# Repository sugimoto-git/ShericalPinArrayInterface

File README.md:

# ShericalPinArrayInterface
球体ピンアレイインターフェースのファームウェア、筐体の3Dデータ、論文を管理する

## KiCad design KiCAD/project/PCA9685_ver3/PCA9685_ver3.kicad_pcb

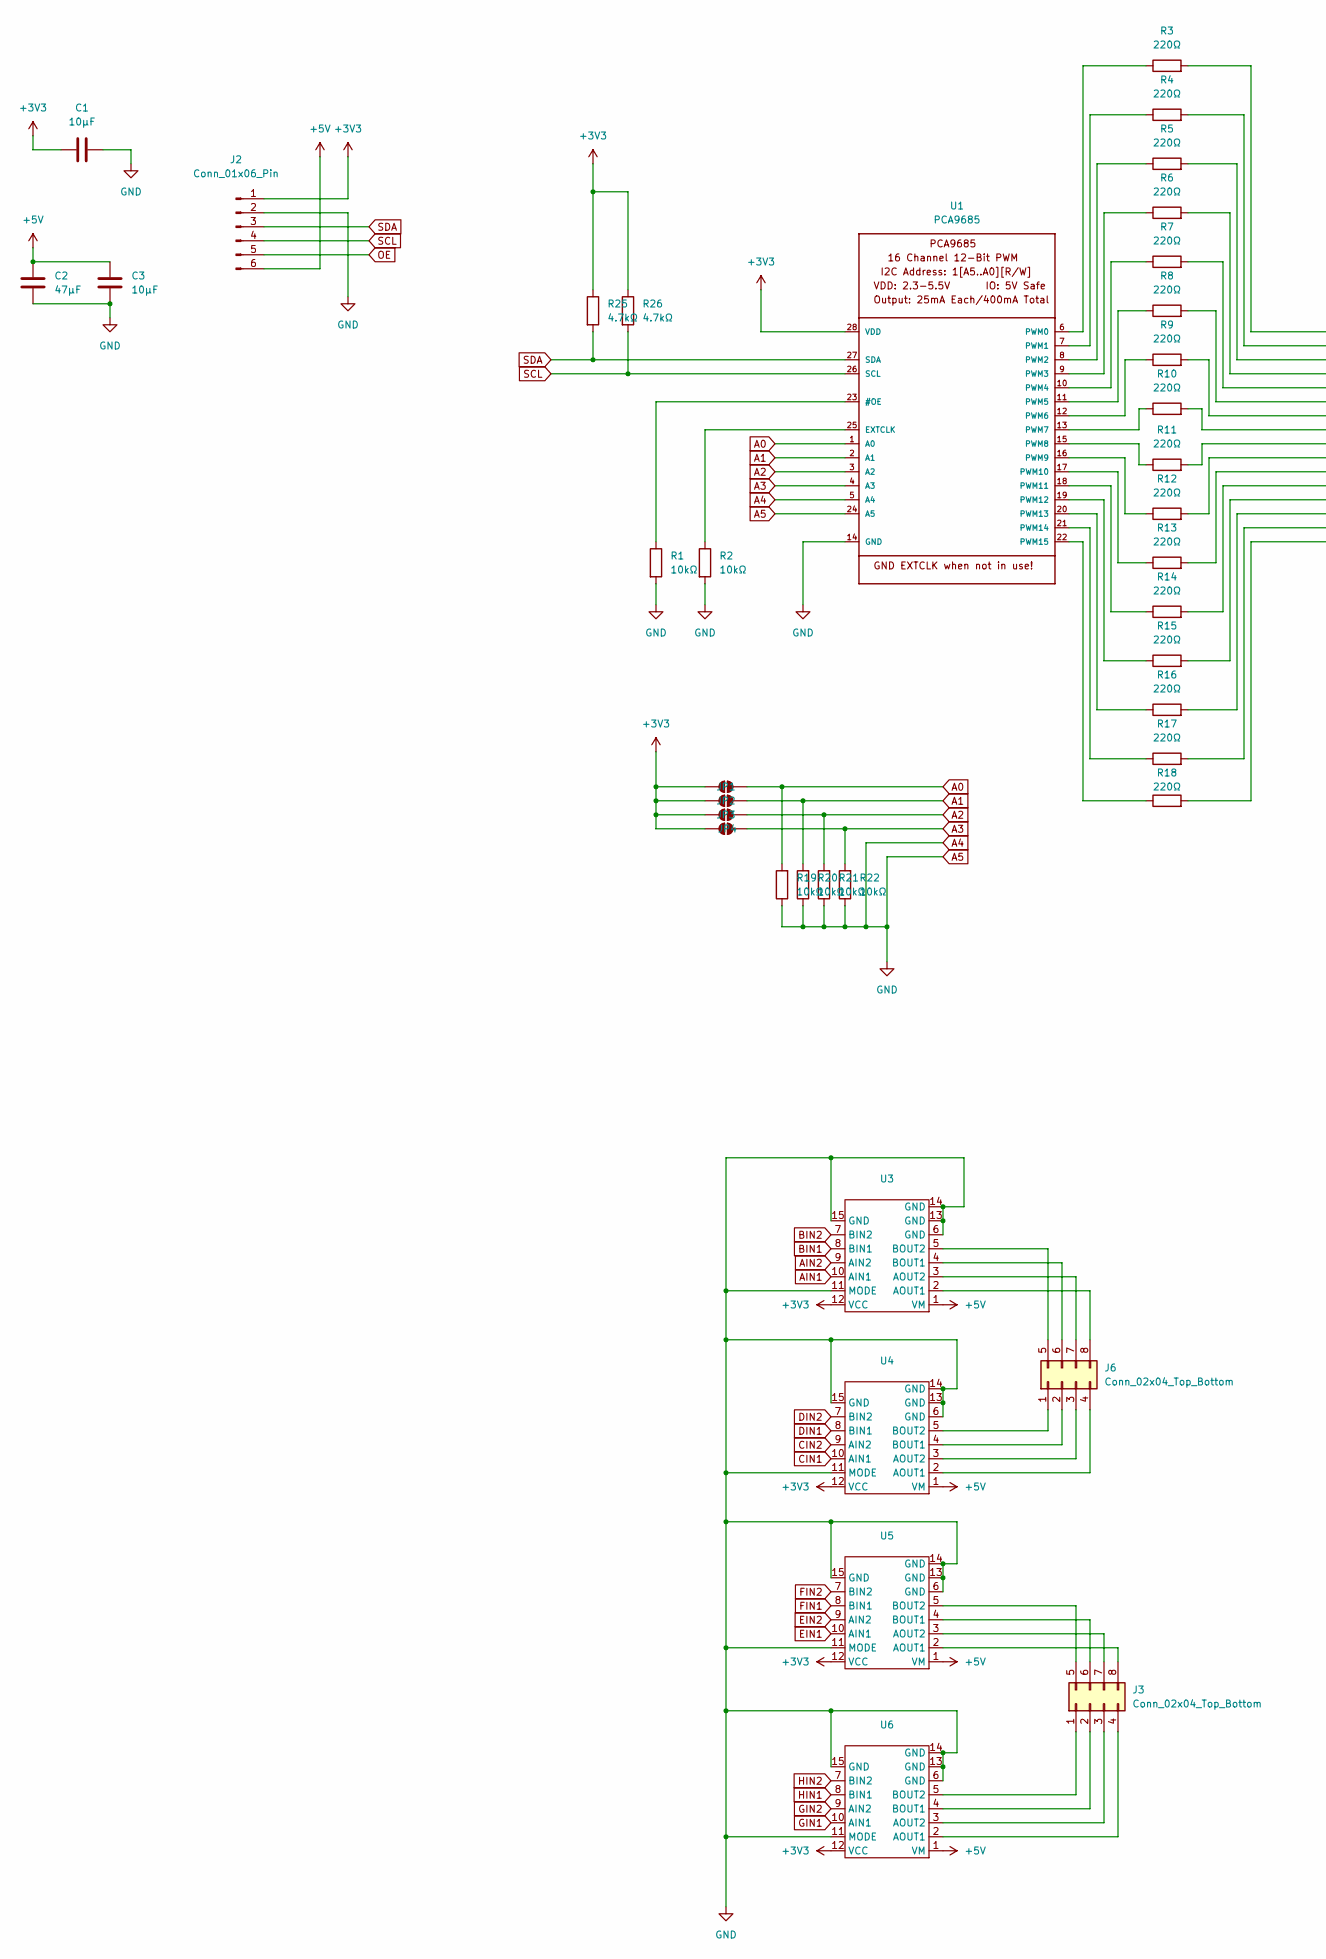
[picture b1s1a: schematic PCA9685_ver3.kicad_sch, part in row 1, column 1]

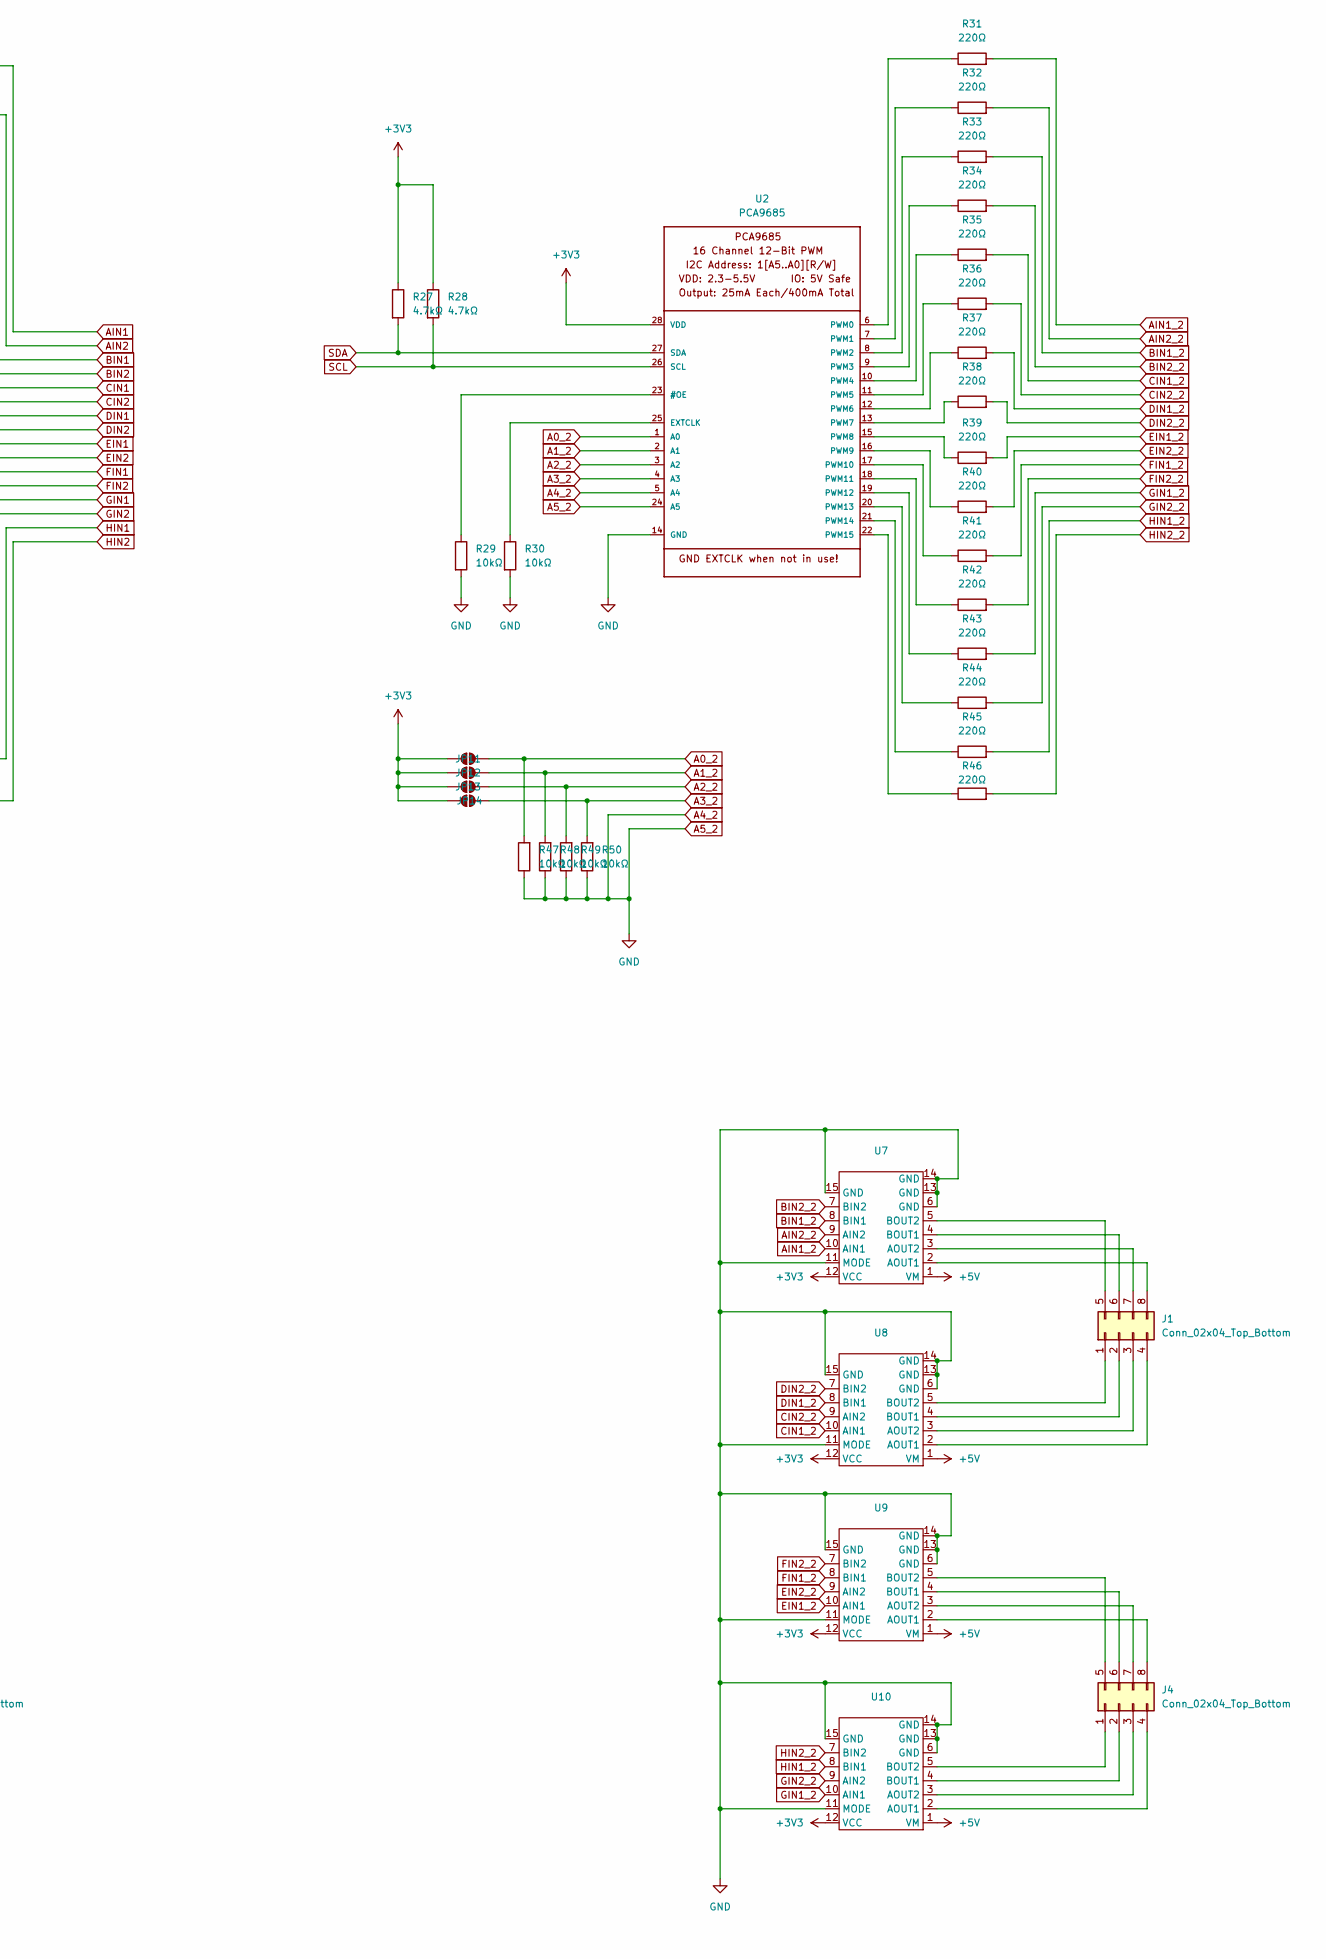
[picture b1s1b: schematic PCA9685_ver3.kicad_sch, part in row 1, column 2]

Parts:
C1, C3: 10μF; C_0603_1608Metric
C2: 47μF; C_0805_2012Metric
J1, J3, J4, J6: Conn_02x04_Top_Bottom; PinHeader_2x04_P2.54mm_Horizontal
J2: Conn_01x06_Pin; PinHeader_1x06_P2.54mm_Horizontal
JP1, JP2, JP3, JP4, JP11, JP12, JP13, JP14: SolderJumper_2_Open; SolderJumper-2_P1.3mm_Open_RoundedPad1.0x1.5mm
R1, R2, R19, R20, R21, R22, R29, R30, R47, R48, R49, R50: 10kΩ; R_0402_1005Metric
R3, R4, R5, R6, R7, R8, R9, R10, R11, R12, R13, R14, R15, R16, R17, R18, R31, R32, R33, R34, R35, R36, R37, R38, R39, R40, R41, R42, R43, R44, R45, R46: 220Ω; R_0402_1005Metric
R25, R26, R27, R28: 4.7kΩ; R_0805_2012Metric
U1, U2: PCA9685; TSSOP-28_4.4x9.7mm_P0.65mm
U3, U4, U5, U6, U7, U8, U9, U10: SON50P300X200X80-13N

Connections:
+3V3: C1.1, J2.1, JP1.1 (A), JP2.1 (A), JP3.1 (A), JP4.1 (A), JP11.1 (A), JP12.1 (A), JP13.1 (A), JP14.1 (A), R25.1, R26.1, R27.1, R28.1, U1.28 (VDD), U2.28 (VDD), U3.12 (VCC), U4.12 (VCC), U5.12 (VCC), U6.12 (VCC), U7.12 (VCC), U8.12 (VCC), U9.12 (VCC), U10.12 (VCC)
+5V: C2.1, C3.1, J2.6, U3.1 (VM), U4.1 (VM), U5.1 (VM), U6.1 (VM), U7.1 (VM), U8.1 (VM), U9.1 (VM), U10.1 (VM)
A0: JP1.2 (B), R19.2, U1.1 (A0)
A0_2: JP11.2 (B), R47.2, U2.1 (A0)
A1: JP2.2 (B), R20.2, U1.2 (A1)
A1_2: JP12.2 (B), R48.2, U2.2 (A1)
A2: JP3.2 (B), R21.2, U1.3 (A2)
A2_2: JP13.2 (B), R49.2, U2.3 (A2)
A3: JP4.2 (B), R22.2, U1.4 (A3)
A3_2: JP14.2 (B), R50.2, U2.4 (A3)
A4: C1.2, C2.2, C3.2, J2.2, R1.2, R2.2, R19.1, R20.1, R21.1, R22.1, R29.2, R30.2, R47.1, R48.1, R49.1, R50.1, U1.5 (A4), U1.14 (GND), U1.24 (A5), U2.5 (A4), U2.14 (GND), U2.24 (A5), U3.6 (GND), U3.11 (MODE), U3.13 (GND), U3.14 (GND), U3.15 (GND), U4.6 (GND), U4.11 (MODE), U4.13 (GND), U4.14 (GND), U4.15 (GND), U5.6 (GND), U5.11 (MODE), U5.13 (GND), U5.14 (GND), U5.15 (GND), U6.6 (GND), U6.11 (MODE), U6.13 (GND), U6.14 (GND), U6.15 (GND), U7.6 (GND), U7.11 (MODE), U7.13 (GND), U7.14 (GND), U7.15 (GND), U8.6 (GND), U8.11 (MODE), U8.13 (GND), U8.14 (GND), U8.15 (GND), U9.6 (GND), U9.11 (MODE), U9.13 (GND), U9.14 (GND), U9.15 (GND), U10.6 (GND), U10.11 (MODE), U10.13 (GND), U10.14 (GND), U10.15 (GND)
AIN1: R3.2, U3.10 (AIN1)
AIN1_2: R31.2, U7.10 (AIN1)
AIN2: R4.2, U3.9 (AIN2)
AIN2_2: R32.2, U7.9 (AIN2)
BIN1: R5.2, U3.8 (BIN1)
BIN1_2: R33.2, U7.8 (BIN1)
BIN2: R6.2, U3.7 (BIN2)
BIN2_2: R34.2, U7.7 (BIN2)
CIN1: R7.2, U4.10 (AIN1)
CIN1_2: R35.2, U8.10 (AIN1)
CIN2: R8.2, U4.9 (AIN2)
CIN2_2: R36.2, U8.9 (AIN2)
DIN1: R9.2, U4.8 (BIN1)
DIN1_2: R37.2, U8.8 (BIN1)
DIN2: R10.2, U4.7 (BIN2)
DIN2_2: R38.2, U8.7 (BIN2)
EIN1: R11.2, U5.10 (AIN1)
EIN1_2: R39.2, U9.10 (AIN1)
EIN2: R12.2, U5.9 (AIN2)
EIN2_2: R40.2, U9.9 (AIN2)
FIN1: R13.2, U5.8 (BIN1)
FIN1_2: R41.2, U9.8 (BIN1)
FIN2: R14.2, U5.7 (BIN2)
FIN2_2: R42.2, U9.7 (BIN2)
GIN1: R15.2, U6.10 (AIN1)
GIN1_2: R43.2, U10.10 (AIN1)
GIN2: R16.2, U6.9 (AIN2)
GIN2_2: R44.2, U10.9 (AIN2)
HIN1: R17.2, U6.8 (BIN1)
HIN1_2: R45.2, U10.8 (BIN1)
HIN2: R18.2, U6.7 (BIN2)
HIN2_2: R46.2, U10.7 (BIN2)
unnamed: J1.1, U8.5 (BOUT2)
unnamed: J1.2, U8.4 (BOUT1)
unnamed: J1.3, U8.3 (AOUT2)
unnamed: J1.4, U8.2 (AOUT1)
unnamed: J1.5, U7.5 (BOUT2)
unnamed: J1.6, U7.4 (BOUT1)
unnamed: J1.7, U7.3 (AOUT2)
unnamed: J1.8, U7.2 (AOUT1)
unnamed: J3.1, U6.5 (BOUT2)
unnamed: J3.2, U6.4 (BOUT1)
unnamed: J3.3, U6.3 (AOUT2)
unnamed: J3.4, U6.2 (AOUT1)
unnamed: J3.5, U5.5 (BOUT2)
unnamed: J3.6, U5.4 (BOUT1)
unnamed: J3.7, U5.3 (AOUT2)
unnamed: J3.8, U5.2 (AOUT1)
unnamed: J4.1, U10.5 (BOUT2)
unnamed: J4.2, U10.4 (BOUT1)
unnamed: J4.3, U10.3 (AOUT2)
unnamed: J4.4, U10.2 (AOUT1)
unnamed: J4.5, U9.5 (BOUT2)
unnamed: J4.6, U9.4 (BOUT1)
unnamed: J4.7, U9.3 (AOUT2)
unnamed: J4.8, U9.2 (AOUT1)
unnamed: J6.1, U4.5 (BOUT2)
unnamed: J6.2, U4.4 (BOUT1)
unnamed: J6.3, U4.3 (AOUT2)
unnamed: J6.4, U4.2 (AOUT1)
unnamed: J6.5, U3.5 (BOUT2)
unnamed: J6.6, U3.4 (BOUT1)
unnamed: J6.7, U3.3 (AOUT2)
unnamed: J6.8, U3.2 (AOUT1)
unnamed: R1.1, U1.23 (#OE)
unnamed: R2.1, U1.25 (EXTCLK)
unnamed: R3.1, U1.6 (PWM0)
unnamed: R4.1, U1.7 (PWM1)
unnamed: R5.1, U1.8 (PWM2)
unnamed: R6.1, U1.9 (PWM3)
unnamed: R7.1, U1.10 (PWM4)
unnamed: R8.1, U1.11 (PWM5)
unnamed: R9.1, U1.12 (PWM6)
unnamed: R10.1, U1.13 (PWM7)
unnamed: R11.1, U1.15 (PWM8)
unnamed: R12.1, U1.16 (PWM9)
unnamed: R13.1, U1.17 (PWM10)
unnamed: R14.1, U1.18 (PWM11)
unnamed: R15.1, U1.19 (PWM12)
unnamed: R16.1, U1.20 (PWM13)
unnamed: R17.1, U1.21 (PWM14)
unnamed: R18.1, U1.22 (PWM15)
unnamed: R29.1, U2.23 (#OE)
unnamed: R30.1, U2.25 (EXTCLK)
unnamed: R31.1, U2.6 (PWM0)
unnamed: R32.1, U2.7 (PWM1)
unnamed: R33.1, U2.8 (PWM2)
unnamed: R34.1, U2.9 (PWM3)
unnamed: R35.1, U2.10 (PWM4)
unnamed: R36.1, U2.11 (PWM5)
unnamed: R37.1, U2.12 (PWM6)
unnamed: R38.1, U2.13 (PWM7)
unnamed: R39.1, U2.15 (PWM8)
unnamed: R40.1, U2.16 (PWM9)
unnamed: R41.1, U2.17 (PWM10)
unnamed: R42.1, U2.18 (PWM11)
unnamed: R43.1, U2.19 (PWM12)
unnamed: R44.1, U2.20 (PWM13)
unnamed: R45.1, U2.21 (PWM14)
unnamed: R46.1, U2.22 (PWM15)
OE: J2.5
SCL: J2.4, R26.2, R28.2, U1.26 (SCL), U2.26 (SCL)
SDA: J2.3, R25.2, R27.2, U1.27 (SDA), U2.27 (SDA)

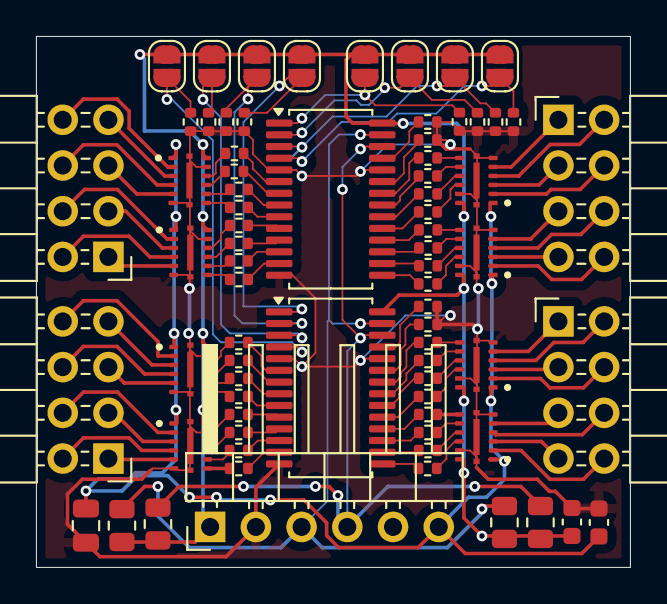
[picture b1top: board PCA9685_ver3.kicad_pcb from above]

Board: 2 copper layers, 33.0 x 29.5 mm, 74 parts (0 on the bottom side), 113 nets.

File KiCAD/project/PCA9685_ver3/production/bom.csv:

Designator,Footprint,Quantity,Value,LCSC Part #
"C1, C3",0603,2,10μF,
C2,0805,1,47μF,
"J1, J3, J4, J6",PinHeader_2x04_P2.54mm_Horizontal,4,Conn_02x04_Top_Bottom,
J2,PinHeader_1x06_P2.54mm_Horizontal,1,Conn_01x06_Pin,
"R1, R19, R2, R20, R21, R22, R29, R30, R47, R48, R49, R50",0402,12,10kΩ,
"R10, R11, R12, R13, R14, R15, R16, R17, R18, R3, R31, R32, R33, R34, R35, R36, R37, R38, R39, R4, R40, R41, R42, R43, R44, R45, R46, R5, R6, R7, R8, R9",0402,32,220Ω,
"R25, R26, R27, R28",0805,4,4.7kΩ,
"U1, U2",TSSOP-28_4.4x9.7mm_P0.65mm,2,PCA9685,
"U10, U3, U4, U5, U6, U7, U8, U9",SON50P300X200X80-13N,8,~,

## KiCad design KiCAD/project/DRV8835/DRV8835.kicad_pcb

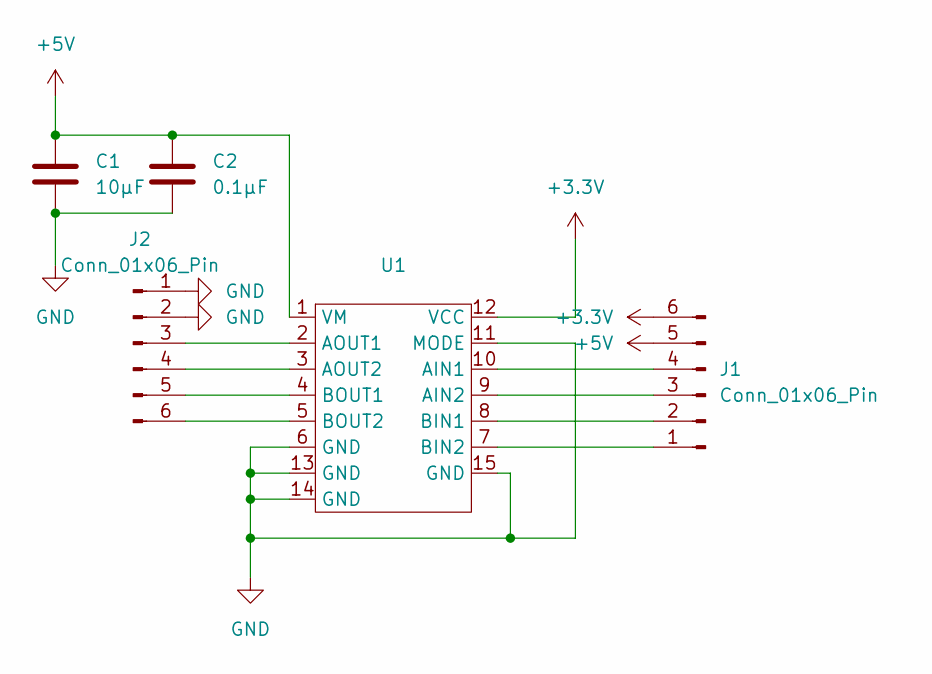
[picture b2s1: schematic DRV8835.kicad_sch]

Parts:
C1: 10μF; C_0805_2012Metric
C2: 0.1μF; C_0805_2012Metric
J1, J2: Conn_01x06_Pin; PinHeader_1x06_P2.54mm_Vertical
U1: SON50P300X200X80-13N

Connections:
+3.3V: J1.6, U1.12 (VCC)
+5V: C1.1, C2.1, J1.5, U1.1 (VM)
GND: C1.2, C2.2, J2.1, J2.2, U1.6 (GND), U1.11 (MODE), U1.13 (GND), U1.14 (GND), U1.15 (GND)
unnamed: J1.1, U1.7 (BIN2)
unnamed: J1.2, U1.8 (BIN1)
unnamed: J1.3, U1.9 (AIN2)
unnamed: J1.4, U1.10 (AIN1)
unnamed: J2.3, U1.2 (AOUT1)
unnamed: J2.4, U1.3 (AOUT2)
unnamed: J2.5, U1.4 (BOUT1)
unnamed: J2.6, U1.5 (BOUT2)

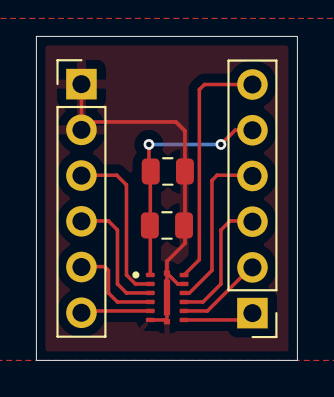
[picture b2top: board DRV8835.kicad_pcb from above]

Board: 2 copper layers, 14.5 x 18.0 mm, 5 parts (0 on the bottom side), 11 nets.

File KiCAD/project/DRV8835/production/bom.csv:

Designator,Footprint,Quantity,Value,LCSC Part #
C1,0805,1,10μF,
C2,0805,1,0.1μF,
"J1, J2",PinHeader_1x06_P2.54mm_Vertical,2,Conn_01x06_Pin,
U1,SON50P300X200X80-13N,1,~,

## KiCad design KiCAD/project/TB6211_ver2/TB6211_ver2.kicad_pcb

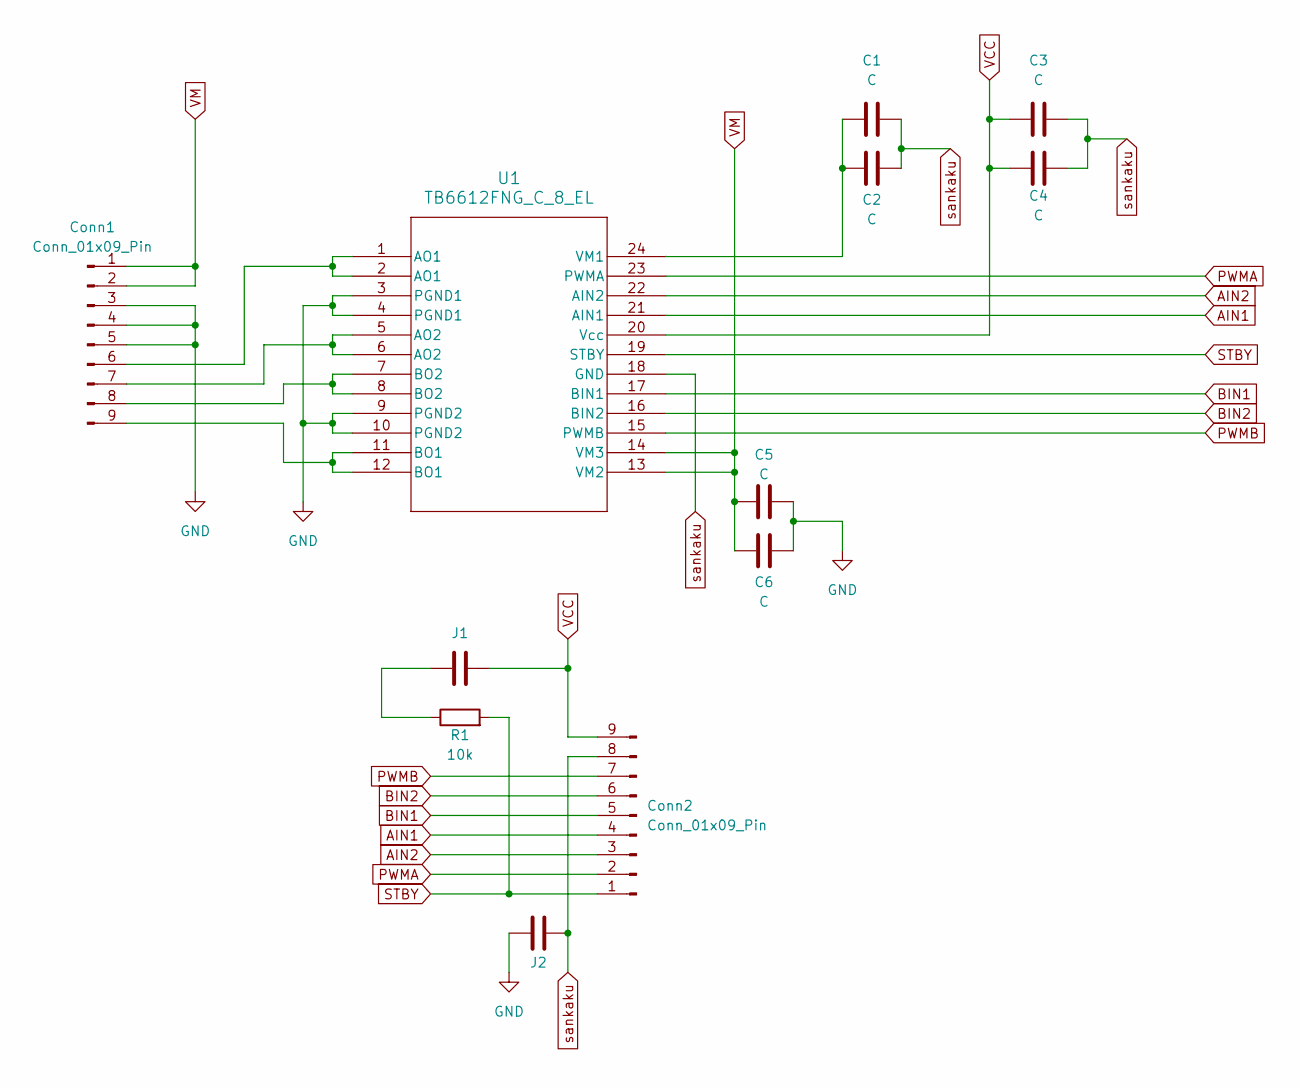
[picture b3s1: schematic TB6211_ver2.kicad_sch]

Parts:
C1, C3, C5: C; C_0201_0603Metric
C2, C4, C6: C; C_0402_1005Metric
Conn1, Conn2: Conn_01x09_Pin; PinHeader_1x09_P2.54mm_Vertical
J1, J2: C; C_0805_2012Metric
R1: 10k; R_0805_2012Metric
U1: TB6612FNG_C_8_EL; SSOP-24_3.9x8.7mm_P0.635mm

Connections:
AIN1: Conn2.4, U1.21 (AIN1)
AIN2: Conn2.3, U1.22 (AIN2)
BIN1: Conn2.5, U1.17 (BIN1)
BIN2: Conn2.6, U1.16 (BIN2)
GND: C5.2, C6.1, Conn1.3, Conn1.4, Conn1.5, J2.1, U1.3 (PGND1), U1.4 (PGND1), U1.9 (PGND2), U1.10 (PGND2)
unnamed: Conn1.6, U1.1 (AO1), U1.2 (AO1)
unnamed: Conn1.7, U1.5 (AO2), U1.6 (AO2)
unnamed: Conn1.8, U1.7 (BO2), U1.8 (BO2)
unnamed: Conn1.9, U1.11 (BO1), U1.12 (BO1)
unnamed: J1.1, R1.1
unnamed: C1.1, C2.1, U1.24 (VM1)
PWMA: Conn2.2, U1.23 (PWMA)
PWMB: Conn2.7, U1.15 (PWMB)
STBY: Conn2.1, R1.2, U1.19 (STBY)
VCC: C3.1, C4.2, Conn2.9, J1.2, U1.20 (Vcc)
VM: C5.1, C6.2, Conn1.1, Conn1.2, U1.13 (VM2), U1.14 (VM3)
sankaku: C1.2, C2.2, C3.2, C4.1, Conn2.8, J2.2, U1.18 (GND)

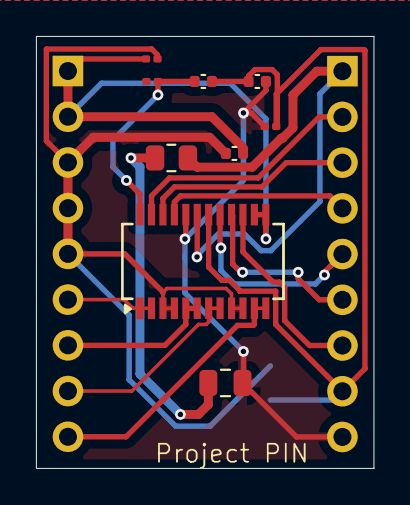
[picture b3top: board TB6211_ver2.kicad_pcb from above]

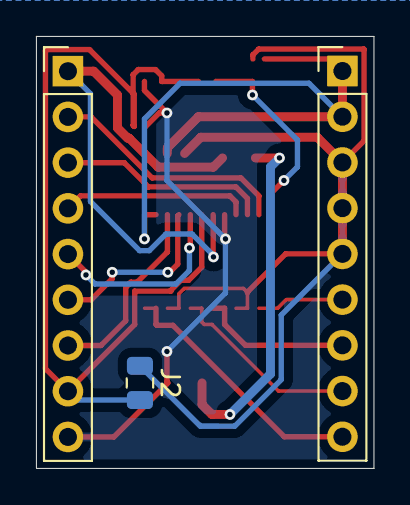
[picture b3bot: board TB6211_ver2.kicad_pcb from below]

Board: 2 copper layers, 18.8 x 24.0 mm, 12 parts (3 on the bottom side), 17 nets.

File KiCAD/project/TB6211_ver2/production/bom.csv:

Designator,Footprint,Quantity,Value,LCSC Part #
"C1, C3, C5",0201,3,C,
"C2, C4, C6",0402,3,C,
"Conn1, Conn2",PinHeader_1x09_P2.54mm_Vertical,2,Conn_01x09_Pin,
"J1, J2",0805,2,C,
R1,0805,1,10k,
U1,SSOP-24_3.9x8.7mm_P0.635mm,1,TB6612FNG_C_8_EL,

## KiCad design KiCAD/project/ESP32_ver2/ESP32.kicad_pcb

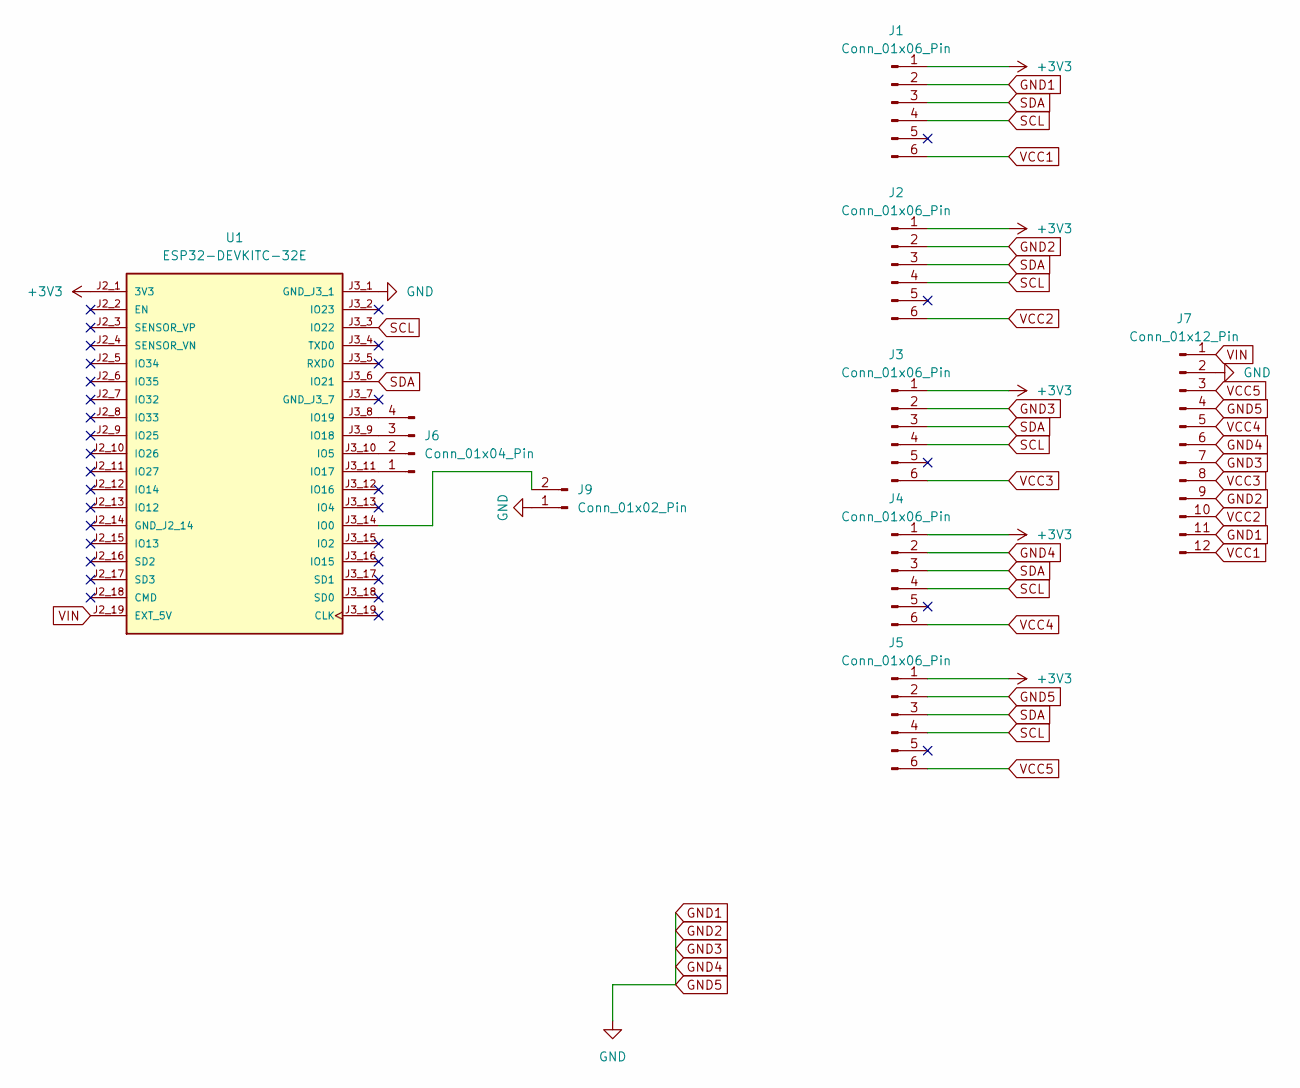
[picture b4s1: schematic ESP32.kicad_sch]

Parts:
J1, J2, J3, J4, J5: Conn_01x06_Pin; PinHeader_1x06_P2.54mm_Vertical
J6: Conn_01x04_Pin; PinHeader_1x04_P2.54mm_Vertical
J7: Conn_01x12_Pin; PinHeader_1x12_P2.54mm_Vertical
J9: Conn_01x02_Pin; PinHeader_1x02_P2.54mm_Vertical
U1: ESP32-DEVKITC-32E; MODULE_ESP32-DEVKITC-32E; PARTREV 1.4

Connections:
+3V3: J1.1, J2.1, J3.1, J4.1, J5.1, U1.J2_1 (3V3)
GND1: J1.2, J2.2, J3.2, J4.2, J5.2, J7.2, J7.4, J7.6, J7.7, J7.9, J7.11, J9.1, U1.J3_1 (GND_J3_1)
unnamed: J6.1, U1.J3_11 (IO17)
unnamed: J6.2, U1.J3_10 (IO5)
unnamed: J6.3, U1.J3_9 (IO18)
unnamed: J6.4, U1.J3_8 (IO19)
unnamed: J9.2, U1.J3_14 (IO0)
SCL: J1.4, J2.4, J3.4, J4.4, J5.4, U1.J3_3 (IO22)
SDA: J1.3, J2.3, J3.3, J4.3, J5.3, U1.J3_6 (IO21)
VCC1: J1.6, J7.12
VCC2: J2.6, J7.10
VCC3: J3.6, J7.8
VCC4: J4.6, J7.5
VCC5: J5.6, J7.3
VIN: J7.1, U1.J2_19 (EXT_5V)

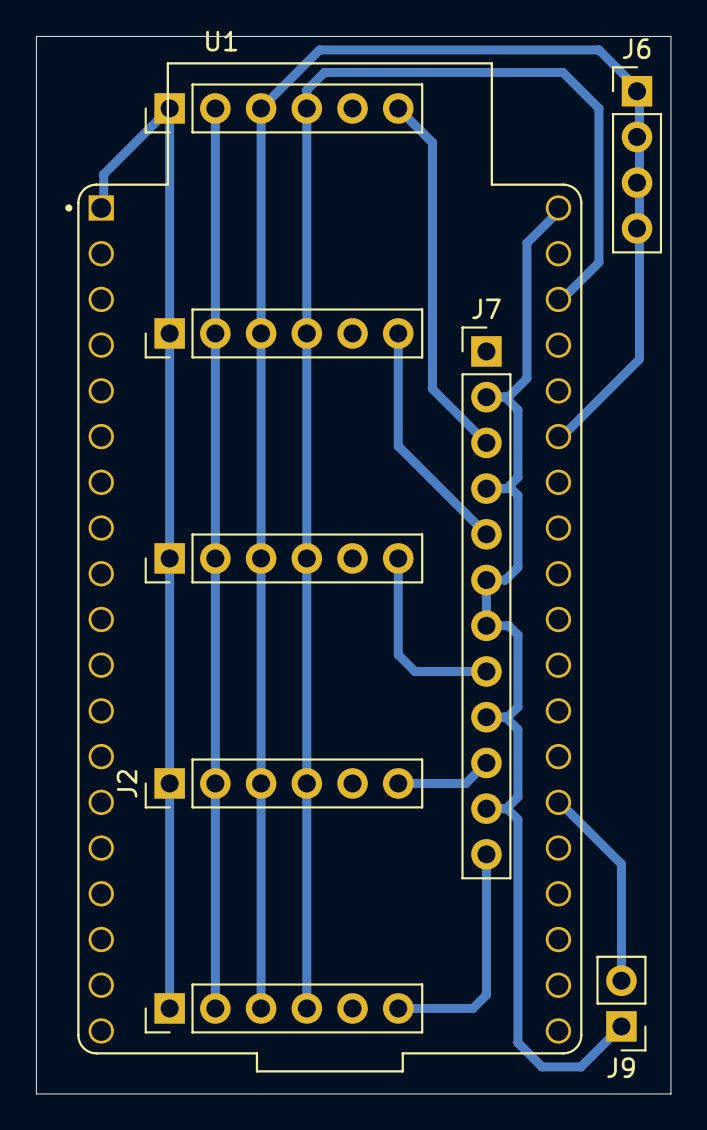
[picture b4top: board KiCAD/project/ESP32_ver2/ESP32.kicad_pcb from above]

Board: 2 copper layers, 35.2 x 58.8 mm, 9 parts (0 on the bottom side), 15 nets.

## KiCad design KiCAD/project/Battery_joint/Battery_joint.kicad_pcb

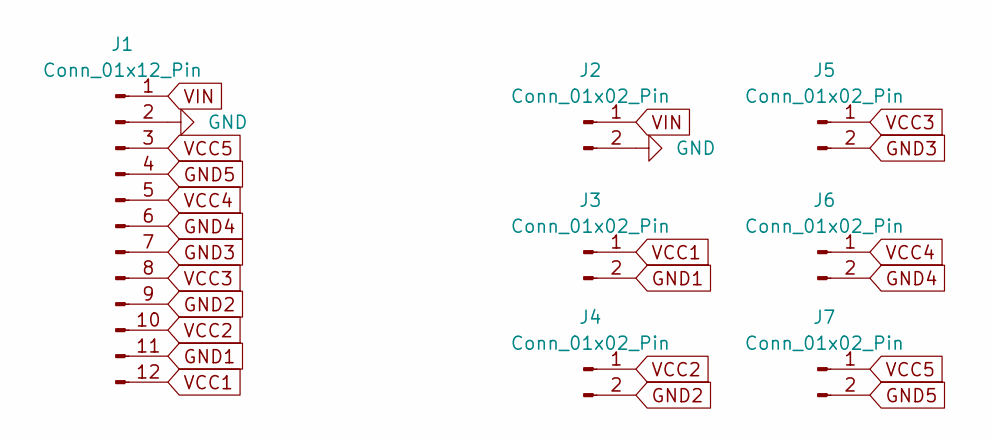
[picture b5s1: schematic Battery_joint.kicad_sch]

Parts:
J1: Conn_01x12_Pin; PinHeader_1x12_P2.54mm_Vertical
J2, J3, J4, J5, J6, J7: Conn_01x02_Pin; PinHeader_1x02_P2.54mm_Vertical

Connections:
GND: J1.2, J2.2
GND1: J1.11, J3.2
GND2: J1.9, J4.2
GND3: J1.7, J5.2
GND4: J1.6, J6.2
GND5: J1.4, J7.2
VCC1: J1.12, J3.1
VCC2: J1.10, J4.1
VCC3: J1.8, J5.1
VCC4: J1.5, J6.1
VCC5: J1.3, J7.1
VIN: J1.1, J2.1

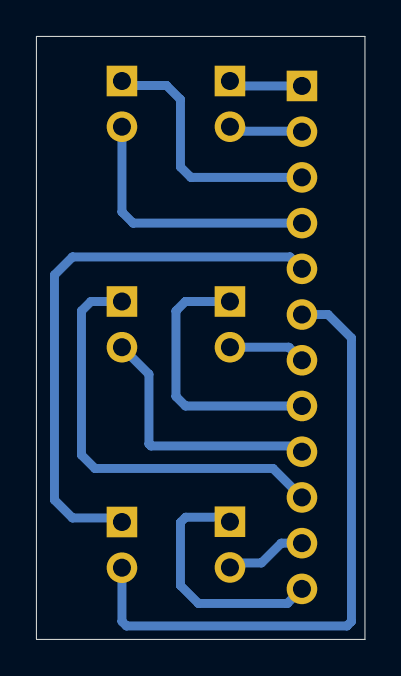
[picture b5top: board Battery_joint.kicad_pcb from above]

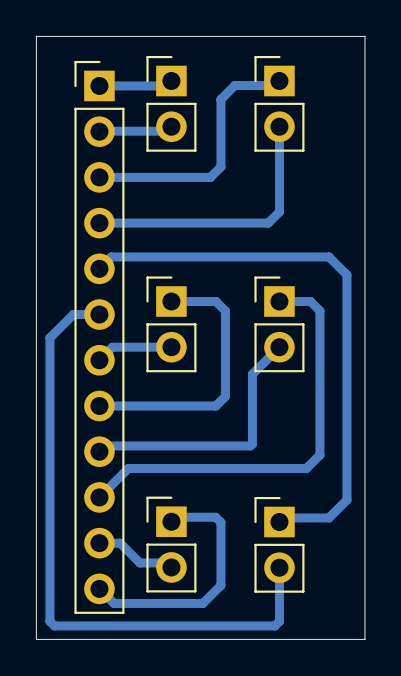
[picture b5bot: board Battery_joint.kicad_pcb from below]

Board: 2 copper layers, 18.2 x 33.5 mm, 7 parts (7 on the bottom side), 12 nets.

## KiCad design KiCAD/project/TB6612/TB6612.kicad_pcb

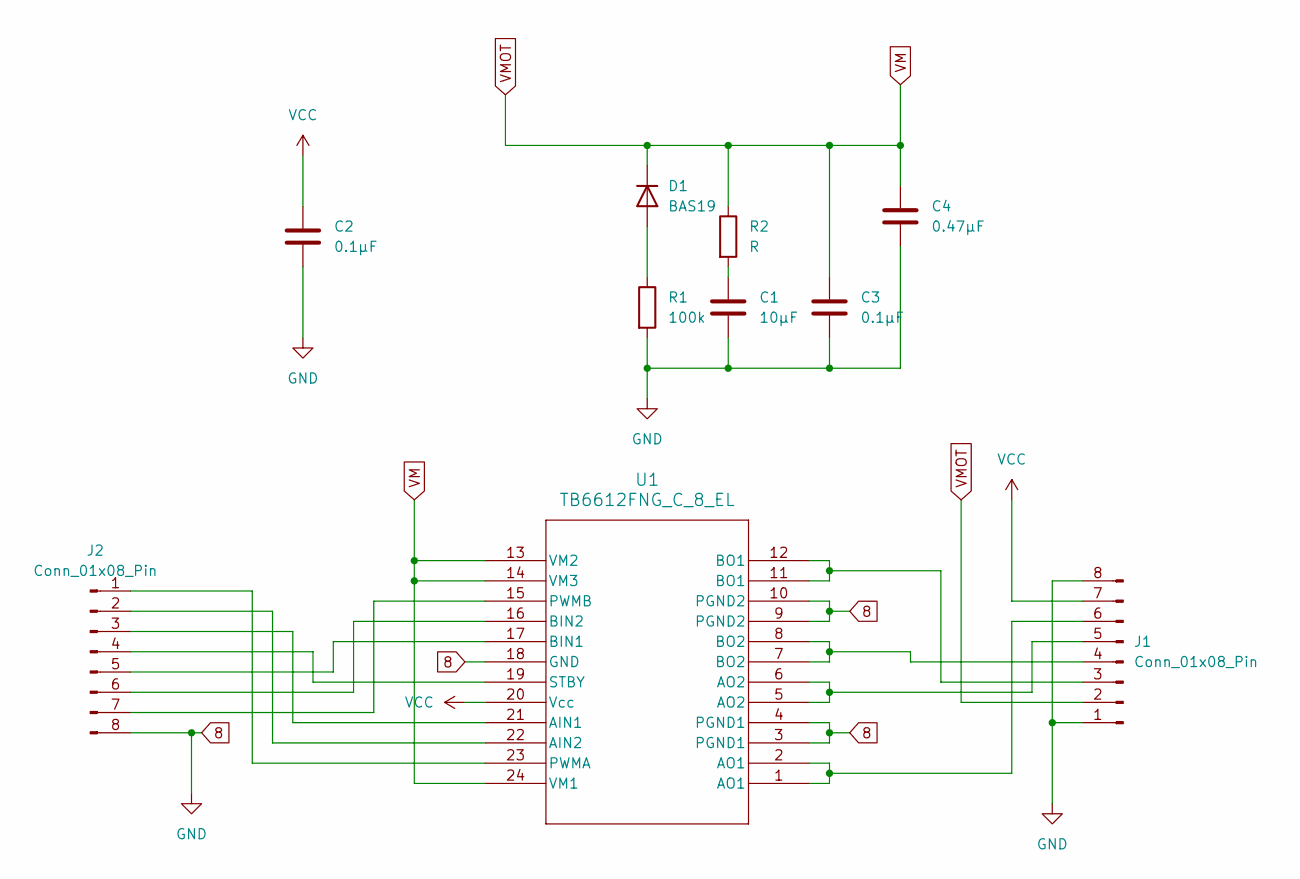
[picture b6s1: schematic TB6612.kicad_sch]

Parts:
C1: 10μF; C_0201_0603Metric
C2, C3: 0.1μF; C_0201_0603Metric
C4: 0.47μF; C_0402_1005Metric
D1: BAS19; SOT-23
J1, J2: Conn_01x08_Pin; JST_EH_B8B-EH-A_1x08_P2.50mm_Vertical
R1: 100k; R_0201_0603Metric
R2: R; R_1206_3216Metric
U1: TB6612FNG_C_8_EL; HTSSOP-24-1EP_4.4x7.8mm_P0.65mm_EP3.2x5mm

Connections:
8: C1.2, C2.2, C3.2, C4.2, J1.1, J1.8, J2.8, R1.2, U1.3 (PGND1), U1.4 (PGND1), U1.9 (PGND2), U1.10 (PGND2), U1.18 (GND)
unnamed: C1.1, R2.2
unnamed: D1.1 (A), R1.1
unnamed: J1.3, U1.11 (BO1), U1.12 (BO1)
unnamed: J1.4, U1.7 (BO2), U1.8 (BO2)
unnamed: J1.5, U1.5 (AO2), U1.6 (AO2)
unnamed: J1.6, U1.1 (AO1), U1.2 (AO1)
unnamed: J2.1, U1.23 (PWMA)
unnamed: J2.2, U1.22 (AIN2)
unnamed: J2.3, U1.21 (AIN1)
unnamed: J2.4, U1.19 (STBY)
unnamed: J2.5, U1.17 (BIN1)
unnamed: J2.6, U1.16 (BIN2)
unnamed: J2.7, U1.15 (PWMB)
VCC: C2.1, J1.7, U1.20 (Vcc)
VM: C3.1, C4.1, D1.3 (K), J1.2, R2.1, U1.13 (VM2), U1.14 (VM3), U1.24 (VM1)

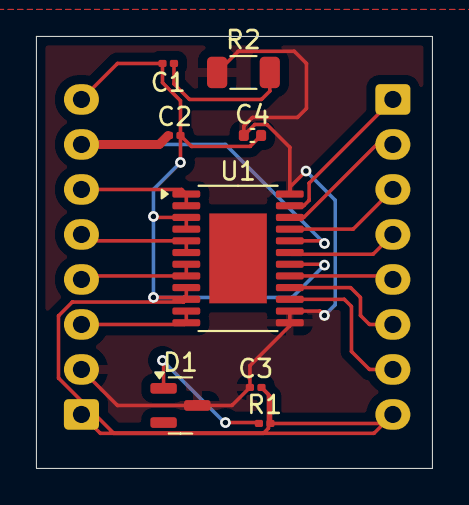
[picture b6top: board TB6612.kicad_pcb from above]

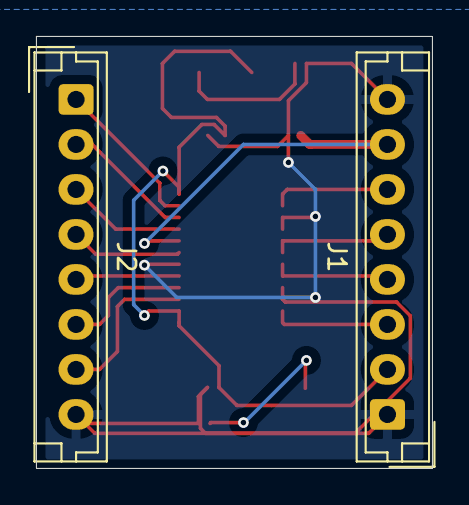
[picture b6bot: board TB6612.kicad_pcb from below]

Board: 2 copper layers, 22.0 x 24.0 mm, 10 parts (2 on the bottom side), 16 nets.

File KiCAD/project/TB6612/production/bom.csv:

Designator,Footprint,Quantity,Value,LCSC Part #
C1,0201,1,10μF,
"C2, C3",0201,2,0.1μF,
C4,0402,1,0.47μF,
D1,SOT-23,1,BAS19,
"J1, J2",JST_EH_B8B-EH-A_1x08_P2.50mm_Vertical,2,Conn_01x08_Pin,
R1,0201,1,100k,
R2,1206,1,R,
U1,HTSSOP-24-1EP_4.4x7.8mm_P0.65mm_EP3.2x5mm,1,TB6612FNG_C_8_EL,

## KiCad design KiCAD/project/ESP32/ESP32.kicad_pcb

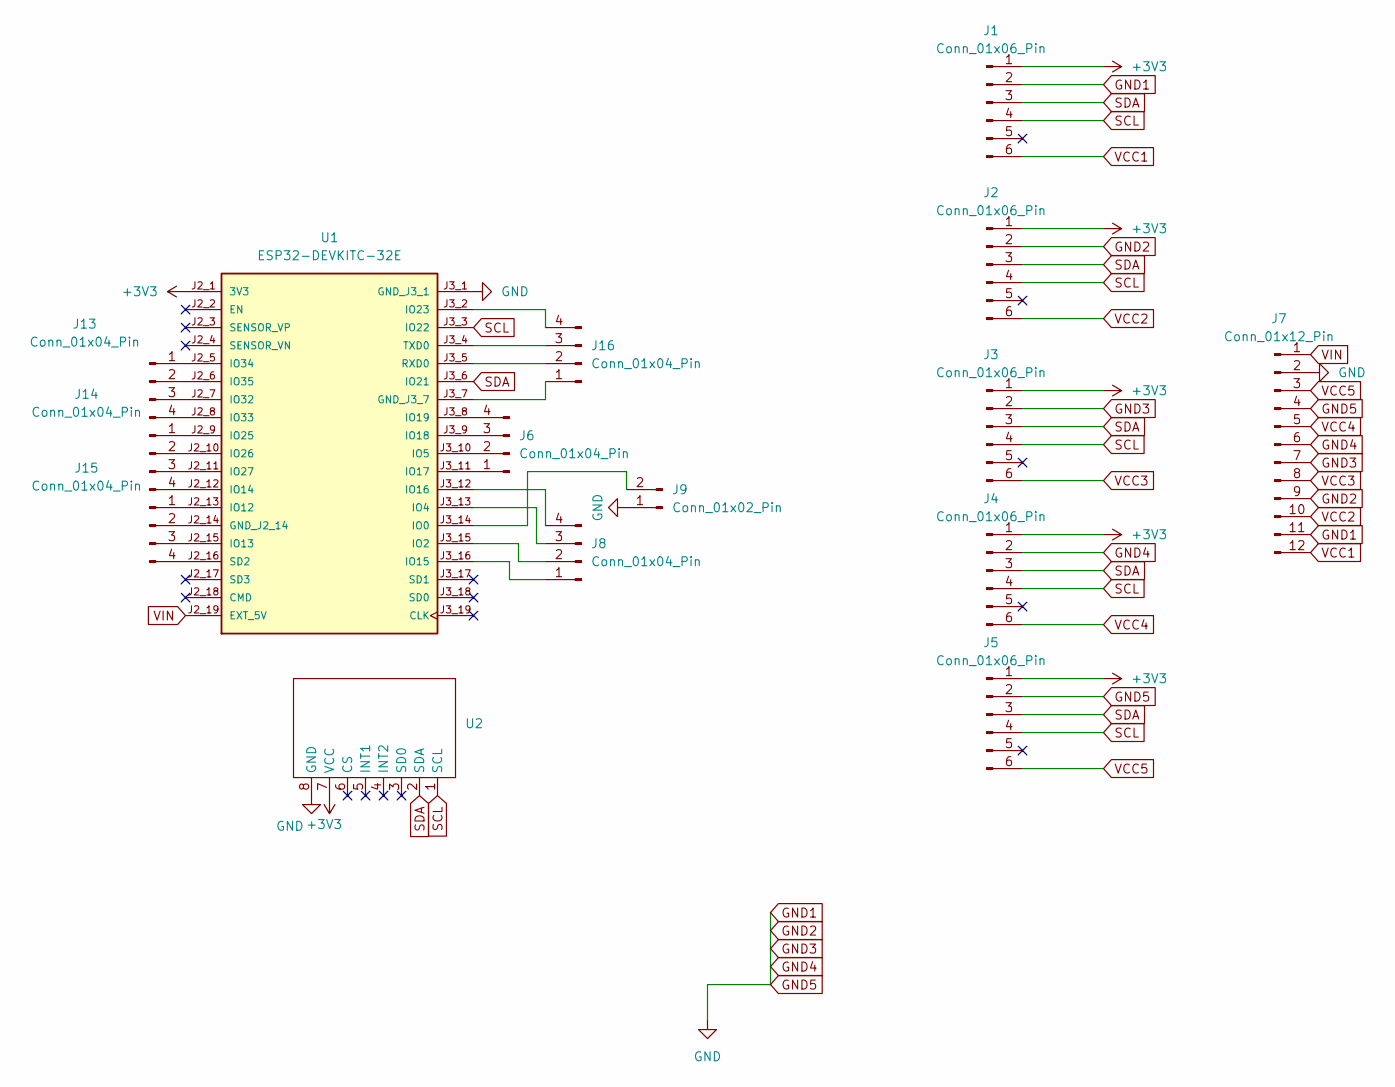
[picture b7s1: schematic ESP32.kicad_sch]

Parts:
J1, J2, J3, J4, J5: Conn_01x06_Pin; PinHeader_1x06_P2.54mm_Vertical
J6, J8, J13, J14, J15, J16: Conn_01x04_Pin; PinHeader_1x04_P2.54mm_Vertical
J7: Conn_01x12_Pin; PinHeader_1x12_P2.54mm_Vertical
J9: Conn_01x02_Pin; PinHeader_1x02_P2.54mm_Vertical
U1: ESP32-DEVKITC-32E; MODULE_ESP32-DEVKITC-32E; PARTREV 1.4
U2: ADXL345

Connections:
+3V3: J1.1, J2.1, J3.1, J4.1, J5.1, U1.J2_1 (3V3), U2.7 (VCC)
GND1: J1.2, J2.2, J3.2, J4.2, J5.2, J7.2, J7.4, J7.6, J7.7, J7.9, J7.11, J9.1, U1.J3_1 (GND_J3_1), U2.8 (GND)
unnamed: J6.1, U1.J3_11 (IO17)
unnamed: J6.2, U1.J3_10 (IO5)
unnamed: J6.3, U1.J3_9 (IO18)
unnamed: J6.4, U1.J3_8 (IO19)
unnamed: J8.1, U1.J3_16 (IO15)
unnamed: J8.2, U1.J3_15 (IO2)
unnamed: J8.3, U1.J3_13 (IO4)
unnamed: J8.4, U1.J3_12 (IO16)
unnamed: J9.2, U1.J3_14 (IO0)
unnamed: J13.1, U1.J2_5 (IO34)
unnamed: J13.2, U1.J2_6 (IO35)
unnamed: J13.3, U1.J2_7 (IO32)
unnamed: J13.4, U1.J2_8 (IO33)
unnamed: J14.1, U1.J2_9 (IO25)
unnamed: J14.2, U1.J2_10 (IO26)
unnamed: J14.3, U1.J2_11 (IO27)
unnamed: J14.4, U1.J2_12 (IO14)
unnamed: J15.1, U1.J2_13 (IO12)
unnamed: J15.2, U1.J2_14 (GND_J2_14)
unnamed: J15.3, U1.J2_15 (IO13)
unnamed: J15.4, U1.J2_16 (SD2)
unnamed: J16.1, U1.J3_7 (GND_J3_7)
unnamed: J16.2, U1.J3_5 (RXD0)
unnamed: J16.3, U1.J3_4 (TXD0)
unnamed: J16.4, U1.J3_2 (IO23)
SCL: J1.4, J2.4, J3.4, J4.4, J5.4, U1.J3_3 (IO22), U2.1 (SCL)
SDA: J1.3, J2.3, J3.3, J4.3, J5.3, U1.J3_6 (IO21), U2.2 (SDA)
VCC1: J1.6, J7.12
VCC2: J2.6, J7.10
VCC3: J3.6, J7.8
VCC4: J4.6, J7.5
VCC5: J5.6, J7.3
VIN: J7.1, U1.J2_19 (EXT_5V)
